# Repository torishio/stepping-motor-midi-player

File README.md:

# ステッピングモータでMIDIを再生できるやつ

stepping-motor-midi-player

USB MIDIで受け取った音を、ステッピングモーターに実際に鳴かせて音にするMIDIシンセサイザー。

**Languages:** [日本語](#日本語) | [English](#english) | [中文](#中文) | [한국어](#한국어)

---

## 日本語

### これは何?

STEPピンをMIDIノートの音程とぴったり同じ周波数でパカパカ切り替えると、ステッピングモーターがその音程で鳴いてくれる(singing stepperってやつ)。この現象を使って、A4988ドライバ+モーター1組を1音分の音源として、DAWやシーケンサーからMIDIで弾けるようにしたもの。各チャンネルにArduinoを1枚使うので、マスター機とかは無し。全部のArduinoが個別にUSB MIDI機器として認識される。

### 中身

- **`firmware/`** — Arduino(Pro Micro互換ボード)に書き込むスケッチ。
  - `stp_motr_channel_velocity/` → こっちが最終版。音程だけじゃなくベロシティ(強弱)もマイクロステップの粗さで表現できる。
  - `stp_motr_channel/` → ベロシティは見てない、シンプルな方。
  - 全チャンネル、同じスケッチを書き込むだけでOK。
- **`hardware/`** — 本番基板(2ch、100×50mm)関連を全部入れてある。
  - **`stp-motr-2ch-100x50-gerbers.zip`** → 製造用データ一式。KiCadすら開かずに、これをJLCPCBとかにそのままアップロードすれば発注できる。
  - `gerbers/` → 上のZIPを展開したやつ。個別に見たい時用。
  - `stp-motr-2ch-100x50.kicad_pro` / `.kicad_sch` / `.kicad_pcb` → 編集・確認したい人向けのKiCadデータ。自作フットプリント/シンボルも `stp_motr.pretty/` `stp_motr.kicad_sym` に同封してるので、これだけで開ける。
  - **`BOM.csv`** → 部品リスト。
  - **`digikey_order.csv`** → Digikeyにそのままインポートできる注文リスト。

### Arduino⇔A4988の配線

1チャンネル分の結線はこんな感じ。他のチャンネルも同じ。

- D4→STEP、D5→DIR、D6→EN(常時LOWでドライバON)
- A0→MS1、A1→MS2、A2→MS3(マイクロステップの切り替え)
- VCC→VDD、GND→GND
- A4988側のRSTとSLPは自分同士でジャンパーするだけ、Arduino側のピンは要らない
- VMOT・コイル出力(1A/1B/2A/2B)・外部+12Vは図から省略(モーター/電源側の配線なので)

### 専用基板を使わず自分で組む場合

基板を起こさずブレッドボードとかで直結したい人向けに、電源・コンデンサ・モーターまで全部含めた回路図も置いてある。

- Arduino側のピンは上と同じ(D4/D5/D6/A0/A1/A2/VCC/GND)
- VMOT-GND間に100&micro;F(低周波の電流供給用)と100nF(PWMノイズ吸収用)を並列で入れる — これが無いとモーターがガキゴカ鳴りやすい
- 外部電源は使うモーターの定格電圧に合わせる(12V用モーターなら12V)
- A4988の1A/1B/2A/2Bをモーターの4本のコイル線に(どっちが1A/1Bかは実際に回してみて逆なら入れ替えればOK)
- Arduino GND・A4988のGND(2本とも)・コンデンサのGND足・外部電源のGND(-)は全部同じ1本のグラウンドとしてつなぐ
- A4988基板上のトリマ(Vref)で電流制限を調整するのを忘れずに。Pololu版(Rsense=0.1&Omega;)なら **Vref=0.8Vで1A制限** になる感じがちょうどいい。ここを合わせないとモーターが熱くなりすぎたり、逆に力が出なかったりする

### 用意するもの

- Arduino Pro Micro互換ボード(ATmega32U4, 5V/16MHz)をチャンネル数分
- Pololu A4988(ヒートシンク付きがおすすめ)をチャンネル数分
- NEMA17クラスのステッピングモーターをチャンネル数分
- 細かい部品は `hardware/BOM.csv` 見てください

### 基板の発注

1. `hardware/stp-motr-2ch-100x50-gerbers.zip` をダウンロード
2. JLCPCBとかPCBWayにそのままアップロード
3. 枚数と色選んで注文するだけ

### 部品の発注

- 全部 `hardware/BOM.csv` に書いてある
- Digikeyで買うなら `hardware/digikey_order.csv` をBOM Managerに突っ込むだけ

### ライセンス

MIT License。`LICENSE` 見てください。

---

## English

### What is this?

If you toggle an A4988's STEP pin at exactly the frequency of a MIDI note's pitch, the stepper motor it's driving will "sing" that pitch — people call this the "singing stepper" trick. This project turns one motor + A4988 pair into a single-voice synth channel, playable live from a DAW or sequencer over USB MIDI. One Arduino per channel, no master board — each one just shows up as its own USB MIDI device.

### What's in here

- **`firmware/`** — sketches for Pro Micro-compatible Arduinos.
  - `stp_motr_channel_velocity/` — the final one. Covers velocity too, not just pitch, by varying how coarse the microstepping is.
  - `stp_motr_channel/` — simpler, pitch-only version.
  - Just flash the same sketch to every channel's board, that's it.
- **`hardware/`** — everything for the actual board (2-channel, 100×50mm).
  - **`stp-motr-2ch-100x50-gerbers.zip`** — the manufacturing files. Upload this straight to JLCPCB or wherever, no need to even open KiCad.
  - `gerbers/` — same thing, already unzipped, if you want to poke at individual files.
  - `stp-motr-2ch-100x50.kicad_pro` / `.kicad_sch` / `.kicad_pcb` — the actual KiCad files if you want to look around or make changes. The custom footprints/symbols are bundled in `stp_motr.pretty/` and `stp_motr.kicad_sym` so it just opens.
  - **`BOM.csv`** — the parts list.
  - **`digikey_order.csv`** — drop this straight into Digikey's order tool.

### Arduino⇔A4988 wiring

Here's how one channel's wiring looks. Every other channel is identical.

- D4→STEP, D5→DIR, D6→EN (held LOW all the time to keep the driver on)
- A0→MS1, A1→MS2, A2→MS3 (microstep selection)
- VCC→VDD, GND→GND
- RST and SLP just jumper to each other on the A4988 — no Arduino pin needed
- VMOT, the coil outputs (1A/1B/2A/2B), and the external +12V are left out of the diagram since that's motor/power wiring, not Arduino wiring

### Building it without the custom board

If you'd rather wire this up on a breadboard or protoboard instead of ordering the PCB, here's the full circuit — power supply, decoupling caps, and motor included.

- Arduino pins are the same as above (D4/D5/D6/A0/A1/A2/VCC/GND)
- Put a 100&micro;F (bulk current) and a 100nF (PWM noise) cap in parallel across VMOT-GND — skip these and the motor tends to buzz
- Match the external supply voltage to your motor's rating (12V motor → 12V supply)
- Wire A4988's 1A/1B/2A/2B to the motor's 4 coil leads (if it spins the wrong way or sounds off, just swap a pair)
- Don't forget to set the current limit via the A4988's onboard trimmer (Vref). For the Pololu board (Rsense = 0.1Ω), **Vref ≈ 0.8V gives roughly a 1A limit** — a good starting point. Skip this and the motor can overheat, or come out too weak.
- Arduino GND, both A4988 GND pins, the cap's ground leg, and the supply's GND/– all need to be the same single ground net

### What you'll need

- One Arduino Pro Micro-compatible board (ATmega32U4, 5V/16MHz) per channel
- One Pololu A4988 (heatsink recommended) per channel
- One NEMA17-class stepper per channel
- Everything else is in `hardware/BOM.csv`

### Ordering the board

1. Grab `hardware/stp-motr-2ch-100x50-gerbers.zip`
2. Upload it to JLCPCB, PCBWay, whatever you use
3. Pick a quantity/color and you're done

### Ordering parts

- It's all in `hardware/BOM.csv`
- Digikey people: just import `hardware/digikey_order.csv` into their BOM Manager

### License

MIT — see `LICENSE`.

---

## 中文

### 这是啥

如果让A4988的STEP引脚正好按某个MIDI音高对应的频率来回切换,它驱动的步进电机就会跟着"唱"出那个音高——大家管这叫"会唱歌的步进电机"。这个项目就是靠这招,把一个电机+A4988凑成一路单音音源,接上USB MIDI就能直接用DAW或音序器弹。每个声部一块Arduino,没有主控这种东西,每块板子自己就是一个独立的USB MIDI设备。

### 里面都有什么

- **`firmware/`** — 刷到Pro Micro兼容板上的程序。
  - `stp_motr_channel_velocity/` — 这是最终版,不只管音高,力度也靠微步细不细来表现。
  - `stp_motr_channel/` — 简化版,没管力度。
  - 每个声部的板子刷同一份程序就行。
- **`hardware/`** — 实际用的那块板子(2通道、100×50mm)的所有东西。
  - **`stp-motr-2ch-100x50-gerbers.zip`** — 生产用的文件,直接传到JLCPCB之类的厂家就能下单,KiCad都不用打开。
  - `gerbers/` — 同样的东西,解压好了,想单独看哪个文件就去这里。
  - `stp-motr-2ch-100x50.kicad_pro` / `.kicad_sch` / `.kicad_pcb` — 想看看电路或者改改的话,这是KiCad源文件。自定义的封装/符号都打包在 `stp_motr.pretty/` 和 `stp_motr.kicad_sym` 里了,打开就能用。
  - **`BOM.csv`** — 物料清单。
  - **`digikey_order.csv`** — 直接丢进Digikey的下单工具就行。

### Arduino与A4988的接线

一个声部的接线大概就是这样,其他声部都一样。

- D4→STEP,D5→DIR,D6→EN(一直拉LOW让驱动器保持开启)
- A0→MS1,A1→MS2,A2→MS3(切换微步模式)
- VCC→VDD,GND→GND
- A4988上的RST和SLP自己接在一起就行,不用占Arduino的引脚
- VMOT、线圈输出(1A/1B/2A/2B)、外部+12V这些电机/电源侧的接线图里没画

### 不用专用板,自己动手接

想用面包板之类的东西直接接线、不打板的话,这里有张包含电源、滤波电容、电机的完整电路图。

- Arduino这边的引脚跟上面一样(D4/D5/D6/A0/A1/A2/VCC/GND)
- VMOT-GND之间并联一个100&micro;F(供大电流用)和一个100nF(吸收PWM噪声用)——不加这俩电机容易嗡嗡响
- 外部电源电压要跟电机的额定电压匹配(12V电机就配12V电源)
- 把A4988的1A/1B/2A/2B接到电机的4根线圈引线上(转反了或者声音不对就随便换一对线试试)
- 别忘了用A4988板上的电位器调电流限制(Vref)。Pololu版(Rsense=0.1Ω)的话,**Vref=0.8V大概对应1A的限制**,这个值挺合适的。不调这个电机容易发热,或者没劲。
- Arduino的GND、A4988的两个GND引脚、电容的接地脚、电源的GND/-,这些都得接成同一个地

### 得准备点啥

- 每个声部一块Arduino Pro Micro兼容板(ATmega32U4,5V/16MHz)
- 每个声部一块Pololu A4988(建议带散热片)
- 每个声部一台NEMA17级步进电机
- 剩下的零件都列在 `hardware/BOM.csv` 里了

### 怎么下单做板子

1. 下载 `hardware/stp-motr-2ch-100x50-gerbers.zip`
2. 传到JLCPCB、PCBWay随便哪家
3. 选数量选颜色,完事

### 怎么买零件

- 都写在 `hardware/BOM.csv` 里
- 用Digikey的话,把 `hardware/digikey_order.csv` 直接导进它的BOM Manager就行

### 许可证

MIT,详见 `LICENSE`。

---

## 한국어

### 이게 뭐냐면

A4988의 STEP 핀을 MIDI 노트 음높이랑 정확히 같은 주파수로 토글해주면, 그 모터가 그 음으로 "노래"를 부른다. 다들 "노래하는 스테퍼"라고 부르는 그 트릭이다. 이걸로 모터+A4988 한 쌍을 음 하나짜리 채널로 만들어서, USB MIDI로 DAW나 시퀀서에서 바로 연주할 수 있게 한 거다. 채널마다 Arduino 한 장씩, 마스터 보드 같은 건 없고 각자 독립된 USB MIDI 장치로 인식된다.

### 들어있는 것

- **`firmware/`** — Pro Micro 호환 보드에 올리는 스케치.
  - `stp_motr_channel_velocity/` — 이게 최종판. 음높이뿐 아니라 벨로시티도 마이크로스텝 거칠기로 표현한다.
  - `stp_motr_channel/` — 벨로시티는 안 보는 단순 버전.
  - 모든 채널 보드에 같은 스케치 올리면 끝.
- **`hardware/`** — 실제 쓰는 보드(2채널, 100×50mm) 관련 전부.
  - **`stp-motr-2ch-100x50-gerbers.zip`** — 제작용 파일 묶음. KiCad 켤 필요도 없이 이걸 JLCPCB 같은 데 바로 올리면 주문된다.
  - `gerbers/` — 같은 걸 풀어놓은 것. 개별 파일 보고 싶을 때.
  - `stp-motr-2ch-100x50.kicad_pro` / `.kicad_sch` / `.kicad_pcb` — 회로 들여다보거나 고치고 싶으면 이 KiCad 파일들. 커스텀 풋프린트/심볼도 `stp_motr.pretty/`랑 `stp_motr.kicad_sym`에 같이 들어있어서 그냥 열면 된다.
  - **`BOM.csv`** — 부품 목록.
  - **`digikey_order.csv`** — Digikey BOM Manager에 그냥 넣으면 되는 주문 리스트.

### Arduino&#8596;A4988 배선

채널 하나의 배선은 이렇게 생겼다. 다른 채널도 다 똑같다.

- D4→STEP, D5→DIR, D6→EN (드라이버를 계속 켜두려고 항상 LOW)
- A0→MS1, A1→MS2, A2→MS3 (마이크로스텝 모드 선택)
- VCC→VDD, GND→GND
- A4988의 RST랑 SLP는 서로 점퍼만 해주면 됨, Arduino 핀은 필요 없음
- VMOT, 코일 출력(1A/1B/2A/2B), 외부 +12V는 모터/전원 쪽 배선이라 그림에서는 뺐음

### 전용 보드 없이 직접 조립하는 경우

PCB 주문 대신 브레드보드 같은 데 직접 배선하고 싶다면, 전원이랑 디커플링 커패시터, 모터까지 다 포함한 전체 회로도도 준비해놨다.

- Arduino 핀은 위랑 똑같음(D4/D5/D6/A0/A1/A2/VCC/GND)
- VMOT-GND 사이에 100&micro;F(대전류용)랑 100nF(PWM 노이즈 제거용) 커패시터를 병렬로 — 이거 없으면 모터가 윙윙거리기 쉬움
- 외부 전원은 쓰는 모터 정격 전압에 맞추기(12V 모터면 12V 전원)
- A4988의 1A/1B/2A/2B를 모터 코일선 4개에 연결(방향이 반대거나 소리가 이상하면 한 쌍만 바꿔 끼워보면 됨)
- A4988 보드의 트리머(Vref)로 전류 제한 맞추는 것도 잊지 말기. Pololu 보드(Rsense=0.1Ω)라면 **Vref=0.8V가 대략 1A 제한**이라 딱 적당하다. 이거 안 맞추면 모터가 너무 뜨거워지거나 힘이 안 나온다.
- Arduino GND, A4988의 GND 두 개, 커패시터 접지 다리, 전원의 GND/- 는 전부 같은 그라운드 하나로 묶어야 함

### 필요한 것

- 채널당 Arduino Pro Micro 호환 보드(ATmega32U4, 5V/16MHz) 1개
- 채널당 Pololu A4988(방열판 추천) 1개
- 채널당 NEMA17급 스테핑 모터 1개
- 나머지는 `hardware/BOM.csv`에 다 있음

### 보드 주문하기

1. `hardware/stp-motr-2ch-100x50-gerbers.zip` 다운로드
2. JLCPCB든 PCBWay든 그대로 업로드
3. 수량/색상 고르고 끝

### 부품 주문하기

- `hardware/BOM.csv`에 다 적혀있음
- Digikey 쓴다면 `hardware/digikey_order.csv`를 BOM Manager에 그대로 넣으면 됨

### 라이선스

MIT. `LICENSE` 참고.

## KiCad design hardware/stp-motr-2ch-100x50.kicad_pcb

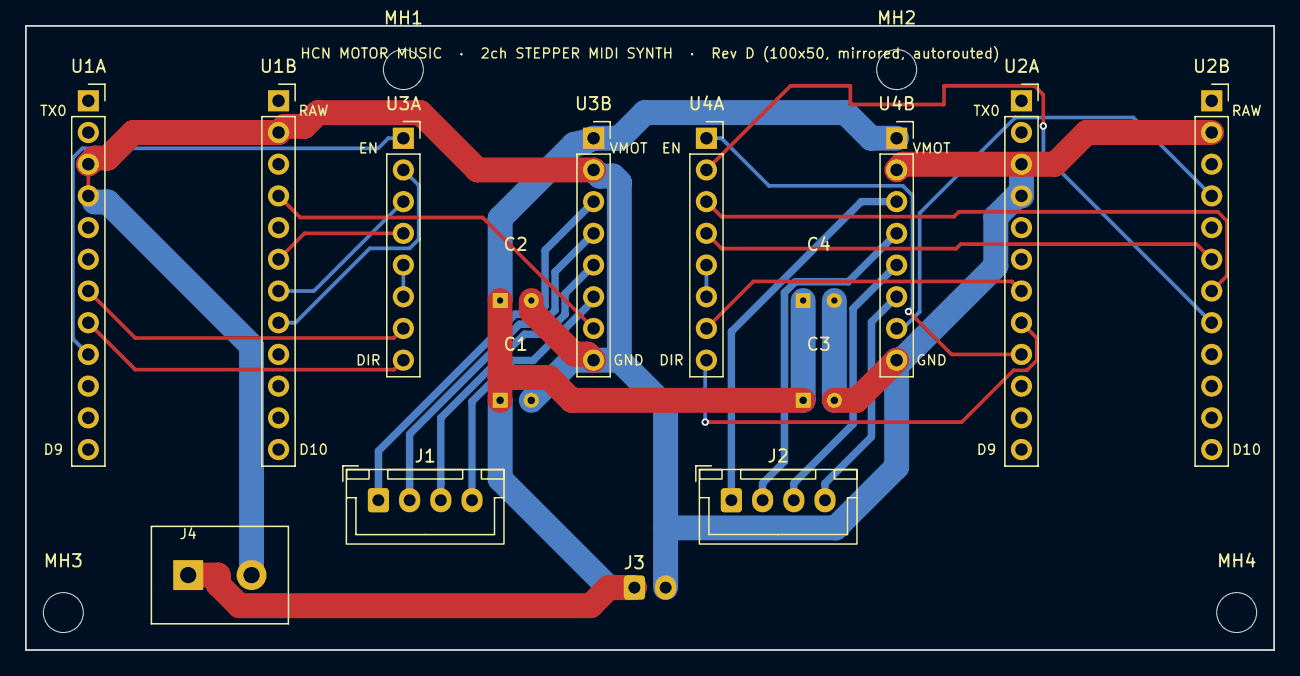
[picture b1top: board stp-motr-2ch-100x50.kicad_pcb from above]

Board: 2 copper layers, 100.0 x 50.0 mm, 20 parts (0 on the bottom side), 26 nets.

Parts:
C1, C3: 100uF 25V THT; CP_Radial_D6.3mm_P2.50mm
C2, C4: 100nF ceramic; C_Disc_D4mm_P2.50mm
J1: Motor 1; JST_XH_B4B-XH-A_1x04_P2.50mm_Vertical
J2: Motor 2; JST_XH_B4B-XH-A_1x04_P2.50mm_Vertical
J3: PWR STACK; JST_XH_B2B-XH-AR_1x02_P2.50mm_RightAngle
J4: PWR TERMINAL; KF301-2P_5.08mm
MH1, MH2, MH3, MH4: MountingHole_3.2mm_M3
U1A: Pro Micro 1L; PinSocket_1x12_P2.54mm_Vertical
U1B: Pro Micro 1R; PinSocket_1x12_P2.54mm_Vertical
U2A: Pro Micro 2L; PinSocket_1x12_P2.54mm_Vertical
U2B: Pro Micro 2R; PinSocket_1x12_P2.54mm_Vertical
U3A: A4988 1 CTRL; PinSocket_1x08_P2.54mm_Vertical
U3B: A4988 1 PWR; PinSocket_1x08_P2.54mm_Vertical
U4A: A4988 2 CTRL; PinSocket_1x08_P2.54mm_Vertical
U4B: A4988 2 PWR; PinSocket_1x08_P2.54mm_Vertical

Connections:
+12V: C1.1, C2.1, C3.1, C4.1, J3.1, J4.1, U3B.1, U4B.1
B1_VCC: U1B.4, U3B.7
B2_VCC: U2B.4, U4B.7
GND: C1.2, C2.2, C3.2, C4.2, J3.2, J4.2, U1A.3, U1A.4, U1B.2, U2A.3, U2A.4, U2B.2, U3B.2, U3B.8, U4B.2, U4B.8
M1_1A: J1.3, U3B.5
M1_1B: J1.4, U3B.6
M1_2A: J1.2, U3B.4
M1_2B: J1.1, U3B.3
M2_1A: J2.3, U4B.5
M2_1B: J2.4, U4B.6
M2_2A: J2.2, U4B.4
M2_2B: J2.1, U4B.3
S1_DIR: U1A.8, U3A.8
S1_EN: U1A.9, U3A.1
S1_MS1: U1B.8, U3A.2
S1_MS2: U1B.7, U3A.3
S1_MS3: U1B.6, U3A.4
S1_RST_SLP: U3A.5, U3A.6
S1_STEP: U1A.7, U3A.7
S2_DIR: U2A.8, U4A.8
S2_EN: U2A.9, U4A.1
S2_MS1: U2B.8, U4A.2
S2_MS2: U2B.7, U4A.3
S2_MS3: U2B.6, U4A.4
S2_RST_SLP: U4A.5, U4A.6
S2_STEP: U2A.7, U4A.7
